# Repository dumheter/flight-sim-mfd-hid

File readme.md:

# Flight Simulation MFD HID.
Physical representation of the buttons around the multi-function display device, to be used in flight simulation games. Note that most airplanes around that time use a similar MFD unit. F-16, F-15, the US version of the Harrier, etc.  
  
The project invoves a custom made PCB, made in Ki-Cad. It's powered by an Arduino pro micro, which uses an Atmel Atmega32u4. It's main strength it the usb controller inside the chip. It will act as a windows joystick device, with 20 buttons that can be mappend in the game to the DDI/MFD.

## How it works
Gif of first test, irl.  
  
Ki-cad pcb drawing.  
  
Finished pcb, next to my flight stick.  
  
How the cockpit look in (dcs) game.

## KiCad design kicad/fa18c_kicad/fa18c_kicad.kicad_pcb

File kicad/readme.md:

I used kicad 6.0, and the pcbway plugin for kicad to automatically export the files to pcbway.

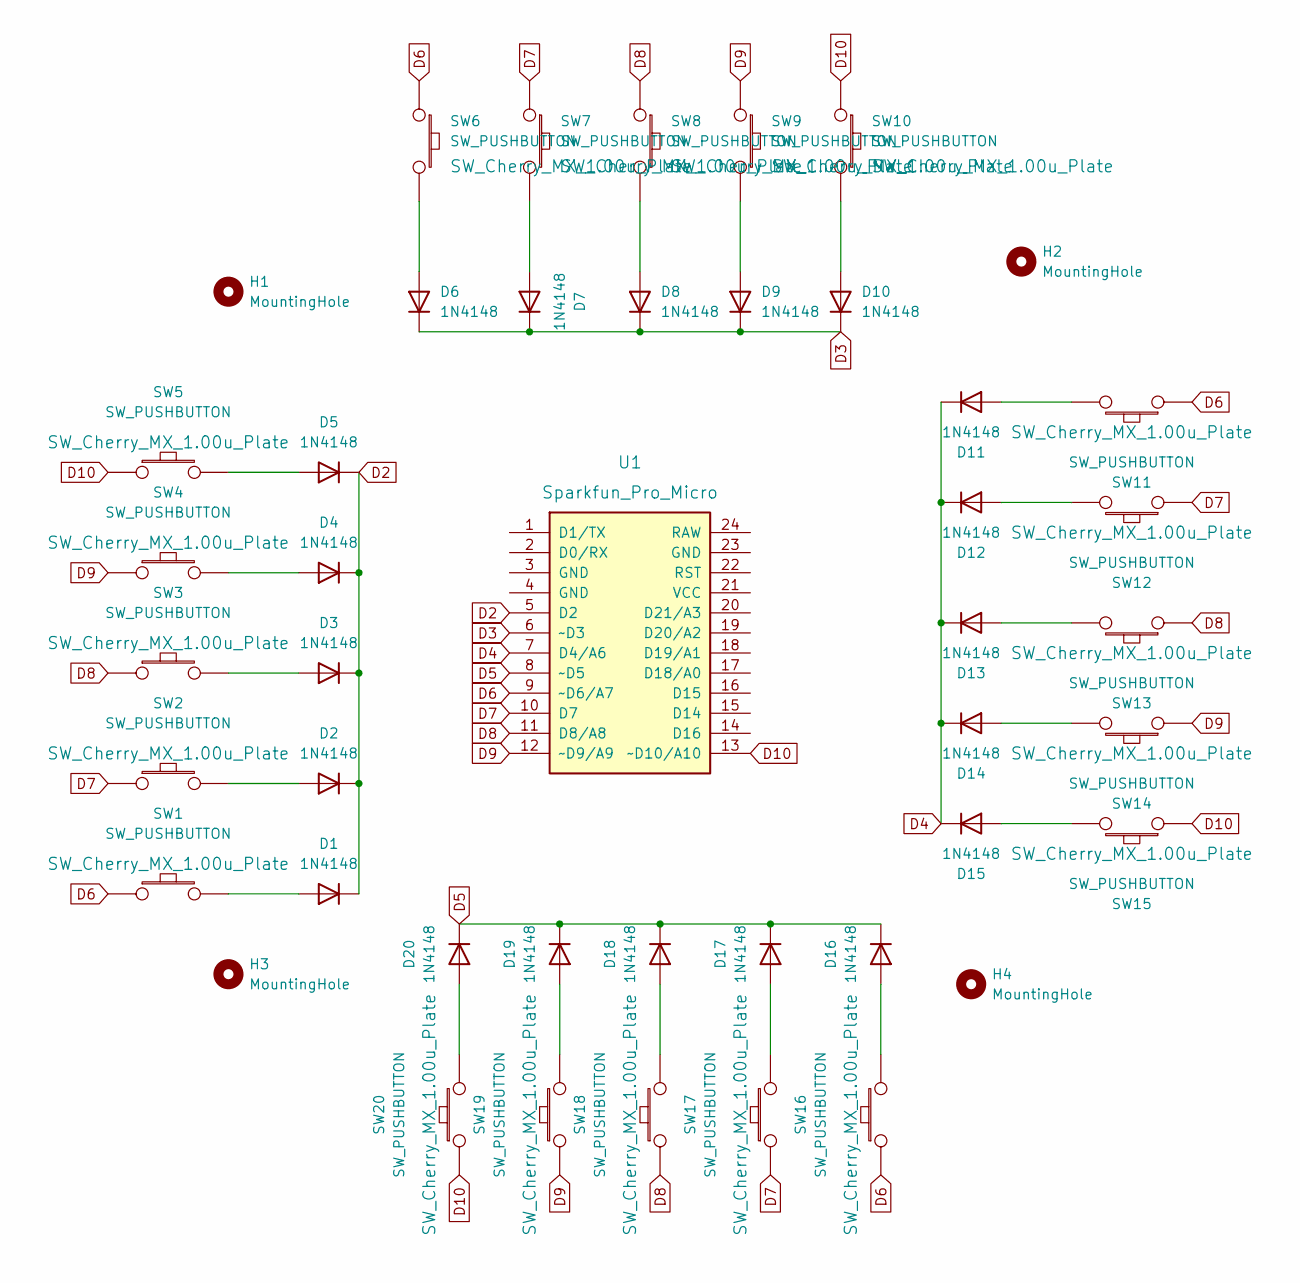
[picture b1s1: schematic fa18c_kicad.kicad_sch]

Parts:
D1, D2, D3, D4, D5, D6, D7, D8, D9, D10, D11, D12, D13, D14, D15, D16, D17, D18, D19, D20: 1N4148; D_DO-35_SOD27_P7.62mm_Horizontal
H1, H2, H3, H4: MountingHole; MountingHole_4mm
SW1, SW2, SW3, SW4, SW5, SW6, SW7, SW8, SW9, SW10, SW11, SW12, SW13, SW14, SW15, SW16, SW17, SW18, SW19, SW20: SW_PUSHBUTTON; SW_Cherry_MX_1.00u_Plate
U1: Sparkfun_Pro_Micro; DIP-24_W15.24mm

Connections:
D2: D1.1 (K), D2.1 (K), D3.1 (K), D4.1 (K), D5.1 (K), U1.5 (D2)
D3: D6.1 (K), D7.1 (K), D8.1 (K), D9.1 (K), D10.1 (K), U1.6 (~D3)
D4: D11.1 (K), D12.1 (K), D13.1 (K), D14.1 (K), D15.1 (K), U1.7 (D4/A6)
D5: D16.1 (K), D17.1 (K), D18.1 (K), D19.1 (K), D20.1 (K), U1.8 (~D5)
D6: SW1.1, SW6.1, SW11.1, SW16.1, U1.9 (~D6/A7)
D7: SW2.1, SW7.1, SW12.1, SW17.1, U1.10 (D7)
D8: SW3.1, SW8.1, SW13.1, SW18.1, U1.11 (D8/A8)
D9: SW4.1, SW9.1, SW14.1, SW19.1, U1.12 (~D9/A9)
D10: SW5.1, SW10.1, SW15.1, SW20.1, U1.13 (~D10/A10)
unnamed: D1.2 (A), SW1.2
unnamed: D2.2 (A), SW2.2
unnamed: D3.2 (A), SW3.2
unnamed: D4.2 (A), SW4.2
unnamed: D5.2 (A), SW5.2
unnamed: D6.2 (A), SW6.2
unnamed: D7.2 (A), SW7.2
unnamed: D8.2 (A), SW8.2
unnamed: D9.2 (A), SW9.2
unnamed: D10.2 (A), SW10.2
unnamed: D11.2 (A), SW11.2
unnamed: D12.2 (A), SW12.2
unnamed: D13.2 (A), SW13.2
unnamed: D14.2 (A), SW14.2
unnamed: D15.2 (A), SW15.2
unnamed: D16.2 (A), SW16.2
unnamed: D17.2 (A), SW17.2
unnamed: D18.2 (A), SW18.2
unnamed: D19.2 (A), SW19.2
unnamed: D20.2 (A), SW20.2

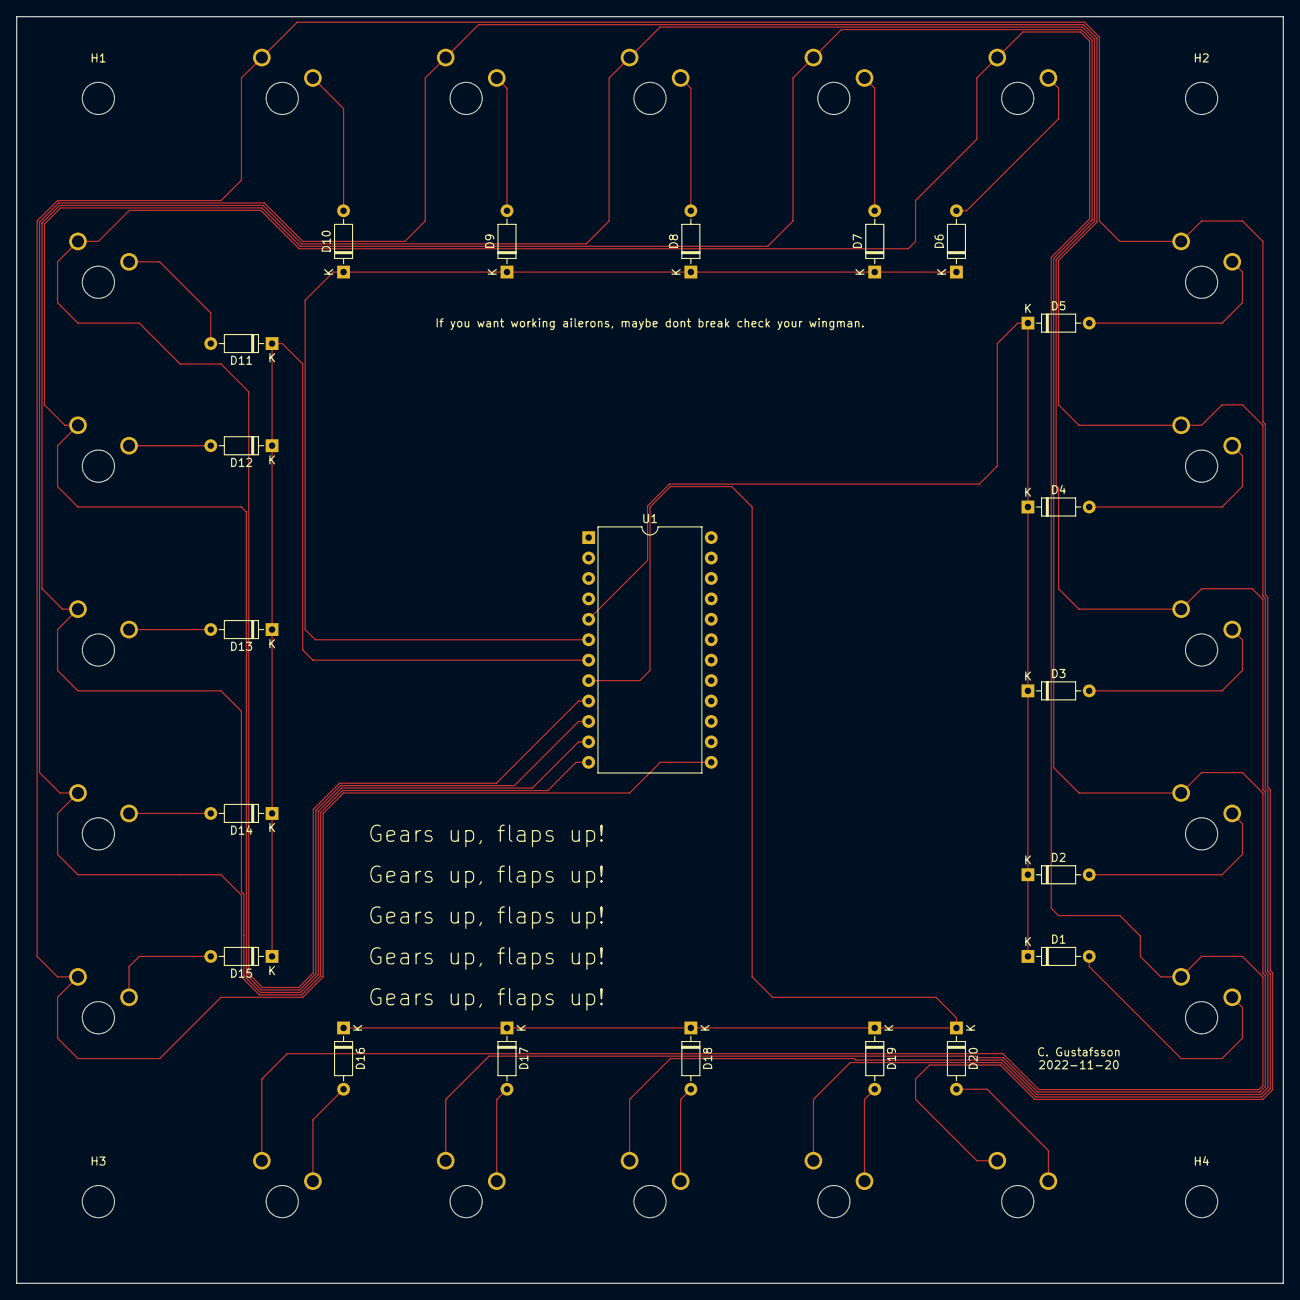
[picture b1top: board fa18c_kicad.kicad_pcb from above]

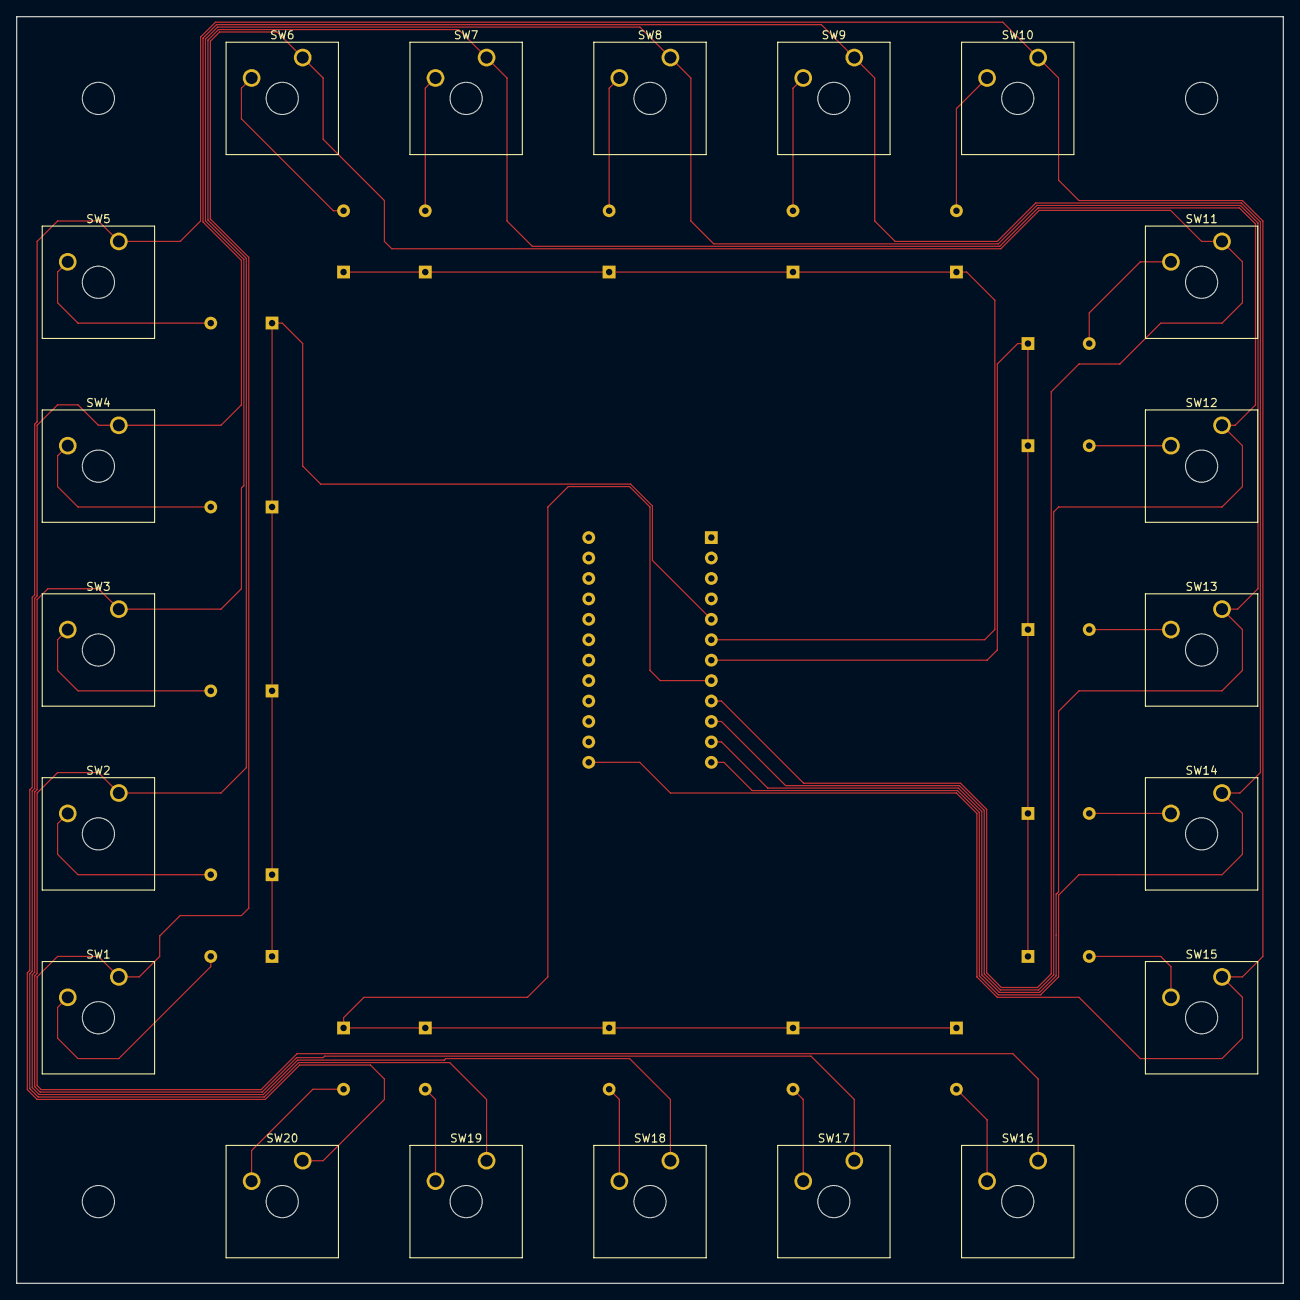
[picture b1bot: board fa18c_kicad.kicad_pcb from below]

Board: 2 copper layers, 157.5 x 157.5 mm, 45 parts (20 on the bottom side), 29 nets.

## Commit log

2023-01-28 init
2023-01-29 Re-write the code to fit a pullup resistor instead of pulldown.
2023-09-24 Designed a case to be 3d printed.
2023-09-24 Fixed mounting hole misaligned.
